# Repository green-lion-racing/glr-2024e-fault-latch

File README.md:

# Fault latch for IMD and BMS/AMS

This board is a fork of [JacobParent7/FSAE_ELECTRONICS](https://github.com/JacobParent7/FSAE_ELECTRONICS/tree/main/Fault%20Latch). Thanks!

### Overview

It is stripped down for our purposes of using it just as a fault latch if either IMD or BMS signal an error. So it can open and close the SDC (Shutdown circuit).

As input it needs +12V and GND. It also takes a high input of both IMD and BMS to register a fault.

It has two outputs for LEDs, these go into the cockpit of the car, to signal issues to the driver.

Lastly there is one connection where the SDC is routed through.

### Used parts

> [!WARNING]  
> Part list is not available currently.

| Article | Description | Link | Quantity |
| ------- | ----------- | ---- | -------- |
|         |             |      |          |
|         |             |      |          |
|         |             |      |          |
|         |             |      |          |
|         |             |      |          |

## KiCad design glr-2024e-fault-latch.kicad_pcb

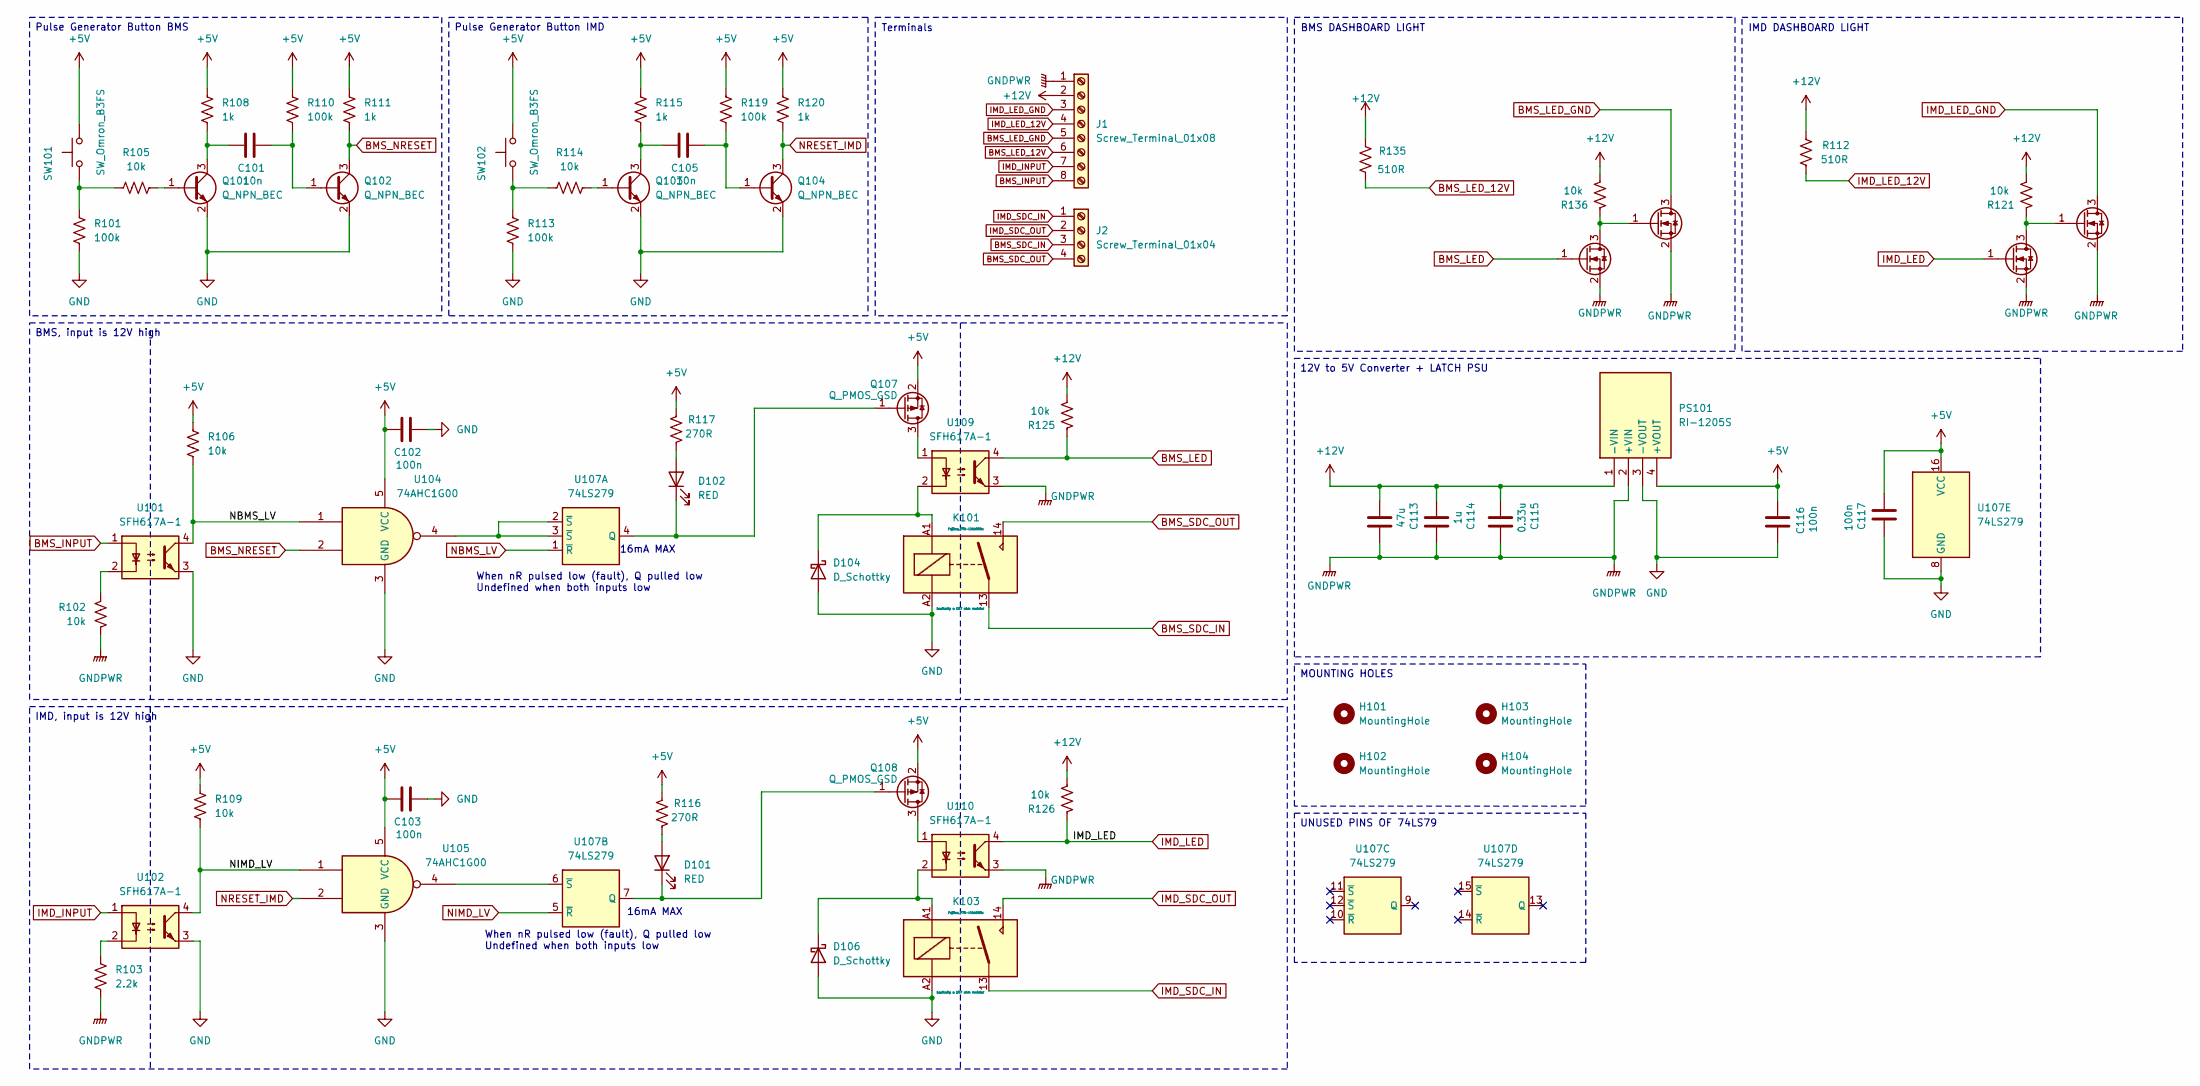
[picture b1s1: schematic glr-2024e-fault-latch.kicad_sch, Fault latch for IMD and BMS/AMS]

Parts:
C101, C105: 10n; C_0603_1608Metric_Pad1.08x0.95mm_HandSolder; JLC# C1589
C102, C103, C116, C117: 100n; C_0603_1608Metric_Pad1.08x0.95mm_HandSolder; JLC# C1591
C113: 47u; CP_Elec_6.3x5.4; JLC# C2836440
C114: 1u; C_0805_2012Metric_Pad1.18x1.45mm_HandSolder; JLC# C91186
C115: 0.33u; C_0603_1608Metric_Pad1.08x0.95mm_HandSolder; JLC# C282682
D101, D102: RED; LED_0805_2012Metric_Pad1.15x1.40mm_HandSolder; JLC# C19171391
D104, D106: D_Schottky; D_SMA; JLC# C8678
H101, H102, H103, H104: MountingHole; MountingHole_3.2mm_M3
J1: Screw_Terminal_01x08; WECO-950-FB-08
J2: Screw_Terminal_01x04; WECO-950-FB-04
K101, K103: Fujitsu_FTR-LYAA005x; Relay_SPST-NO_Fujitsu_FTR-LYAA005x_FormA_Vertical; MOUSER 817-FTR-LYAA005Y
PS101: RI-1205S; RI0505S; Mouser Part Number 919-RI-1205S
Q101, Q102, Q103, Q104: Q_NPN_BEC; SOT-23; JLC# C2146
Q105, Q106, Q114, Q115: Q_NMOS_GSD; SOT-23; JLC# C151421
Q107, Q108: Q_PMOS_GSD; SOT-523; JLC# C96676
R101, R110, R113, R119: 100k; R_0805_2012Metric_Pad1.20x1.40mm_HandSolder; JLC# C149504
R102, R106, R109, R121, R125, R126, R136: 10k; R_0805_2012Metric_Pad1.20x1.40mm_HandSolder; MOUSER ESR10EZPD1002
R103: 2.2k; R_0805_2012Metric_Pad1.20x1.40mm_HandSolder; JLC# C17520
R105, R114: 10k; R_0805_2012Metric_Pad1.20x1.40mm_HandSolder; JLC# C17414
R108, R111, R115, R120: 1k; R_0805_2012Metric_Pad1.20x1.40mm_HandSolder; JLC# C17513
R112, R135: 510R; R_0603_1608Metric; MOUSER KTR03EZPF5100
R116, R117: 270R; R_0805_2012Metric_Pad1.20x1.40mm_HandSolder; JLC# C17590
SW101, SW102: SW_Omron_B3FS; SW_SPST_Omron_B3FS-100xP; JLC# C271750
U101, U102, U109, U110: SFH617A-1; DIP-4_W7.62mm; MOUSER SFH617A-1X007T
U104, U105: 74AHC1G00; SOT-23-5; JLC# C350556
U107: 74LS279; SOIC-16_3.9x9.9mm_P1.27mm; MOUSER 595-SN74LS279ADR

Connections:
+5V: C102.1, C103.1, C116.2, C117.1, PS101.4 (+VOUT), Q107.2 (S), Q108.2 (S), R106.1, R108.1, R109.1, R110.1, R111.1, R115.1, R116.2, R117.2, R119.1, R120.1, SW101.2, SW102.2, U104.5 (VCC), U105.5 (VCC), U107.16 (VCC)
+12V: C113.2, C114.2, C115.2, J1.2, PS101.1 (-VIN), R112.1, R121.1, R125.1, R126.1, R135.1, R136.1
BMS_INPUT: J1.8, U101.1
BMS_LED: Q114.1 (G), R125.2, U109.4
BMS_LED_12V: J1.6, R135.2
BMS_LED_GND: J1.5, Q115.3 (D)
BMS_NRESET: Q102.3 (C), R111.2, U104.2
BMS_SDC_IN: J2.3, K101.13
BMS_SDC_OUT: J2.4, K101.14
GND: C102.2, C103.2, C116.1, C117.2, D104.2 (A), D106.2 (A), K101.A2, K103.A2, PS101.3 (-VOUT), Q101.2 (E), Q102.2 (E), Q103.2 (E), Q104.2 (E), R101.2, R113.2, U101.3, U102.3, U104.3 (GND), U105.3 (GND), U107.8 (GND)
GNDPWR: C113.1, C114.1, C115.1, J1.1, PS101.2 (+VIN), Q105.2 (S), Q106.2 (S), Q114.2 (S), Q115.2 (S), R102.1, R103.2, U109.3, U110.3
IMD_INPUT: J1.7, U102.1
IMD_LED: Q105.1 (G), R126.2, U110.4
IMD_LED_12V: J1.4, R112.2
IMD_LED_GND: J1.3, Q106.3 (D)
IMD_SDC_IN: J2.1, K103.13
IMD_SDC_OUT: J2.2, K103.14
NBMS_LV: R106.2, U101.4, U104.1, U107.1 (~R)
NIMD_LV: R109.2, U102.4, U105.1, U107.5 (~R)
NRESET_IMD: Q104.3 (C), R120.2, U105.2
unnamed: D101.2 (A), R116.1
unnamed: D101.1 (K), Q108.1 (G), U107.7 (Q)
unnamed: D102.2 (A), R117.1
unnamed: D102.1 (K), Q107.1 (G), U107.4 (Q)
unnamed: D104.1 (K), K101.A1, U109.2
unnamed: D106.1 (K), K103.A1, U110.2
unnamed: Q101.1 (B), R105.1
unnamed: C101.1, Q101.3 (C), R108.2
unnamed: C101.2, Q102.1 (B), R110.2
unnamed: Q103.1 (B), R114.1
unnamed: C105.1, Q103.3 (C), R115.2
unnamed: C105.2, Q104.1 (B), R119.2
unnamed: Q105.3 (D), Q106.1 (G), R121.2
unnamed: Q107.3 (D), U109.1
unnamed: Q108.3 (D), U110.1
unnamed: Q114.3 (D), Q115.1 (G), R136.2
unnamed: R101.1, R105.2, SW101.1
unnamed: R102.2, U101.2
unnamed: R103.1, U102.2
unnamed: R113.1, R114.2, SW102.1
unnamed: U104.4, U107.2 (~S), U107.3 (~S)
unnamed: U105.4, U107.6 (~S)

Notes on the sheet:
16mA MAX
When nR pulsed low (fault), Q pulled low Undefined when both inputs low
BMS, input is 12V high
Pulse Generator Button BMS
Terminals
UNUSED PINS OF 74LS79
Pulse Generator Button IMD
12V to 5V Converter + LATCH PSU
MOUNTING HOLES
BMS DASHBOARD LIGHT
IMD, input is 12V high
IMD DASHBOARD LIGHT

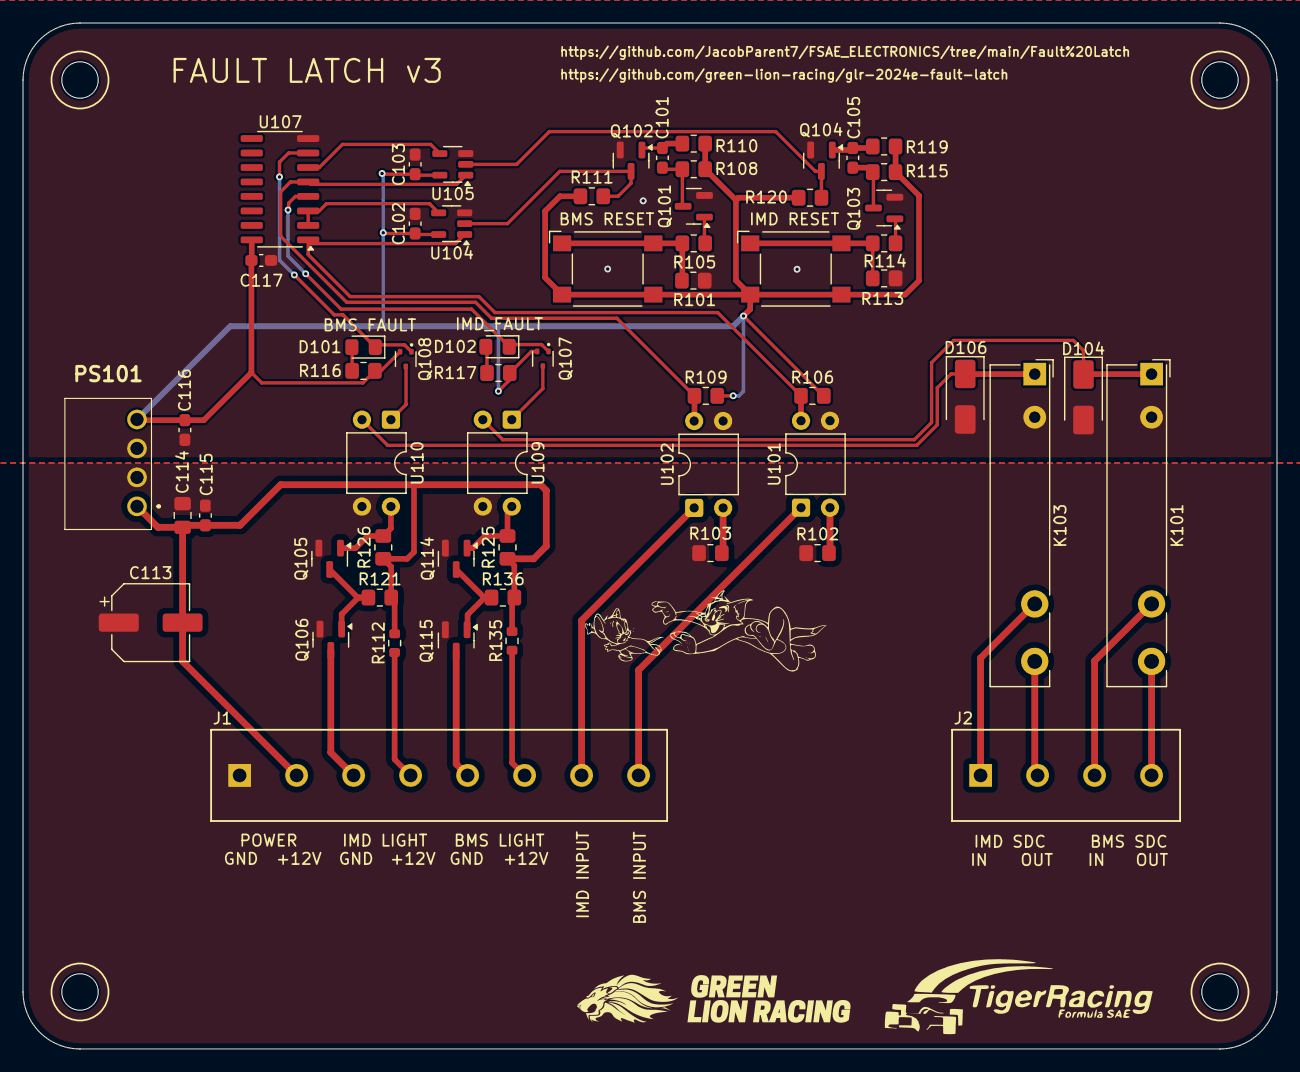
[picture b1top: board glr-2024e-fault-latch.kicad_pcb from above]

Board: 2 copper layers, 110.0 x 90.0 mm, 63 parts (0 on the bottom side), 42 nets.

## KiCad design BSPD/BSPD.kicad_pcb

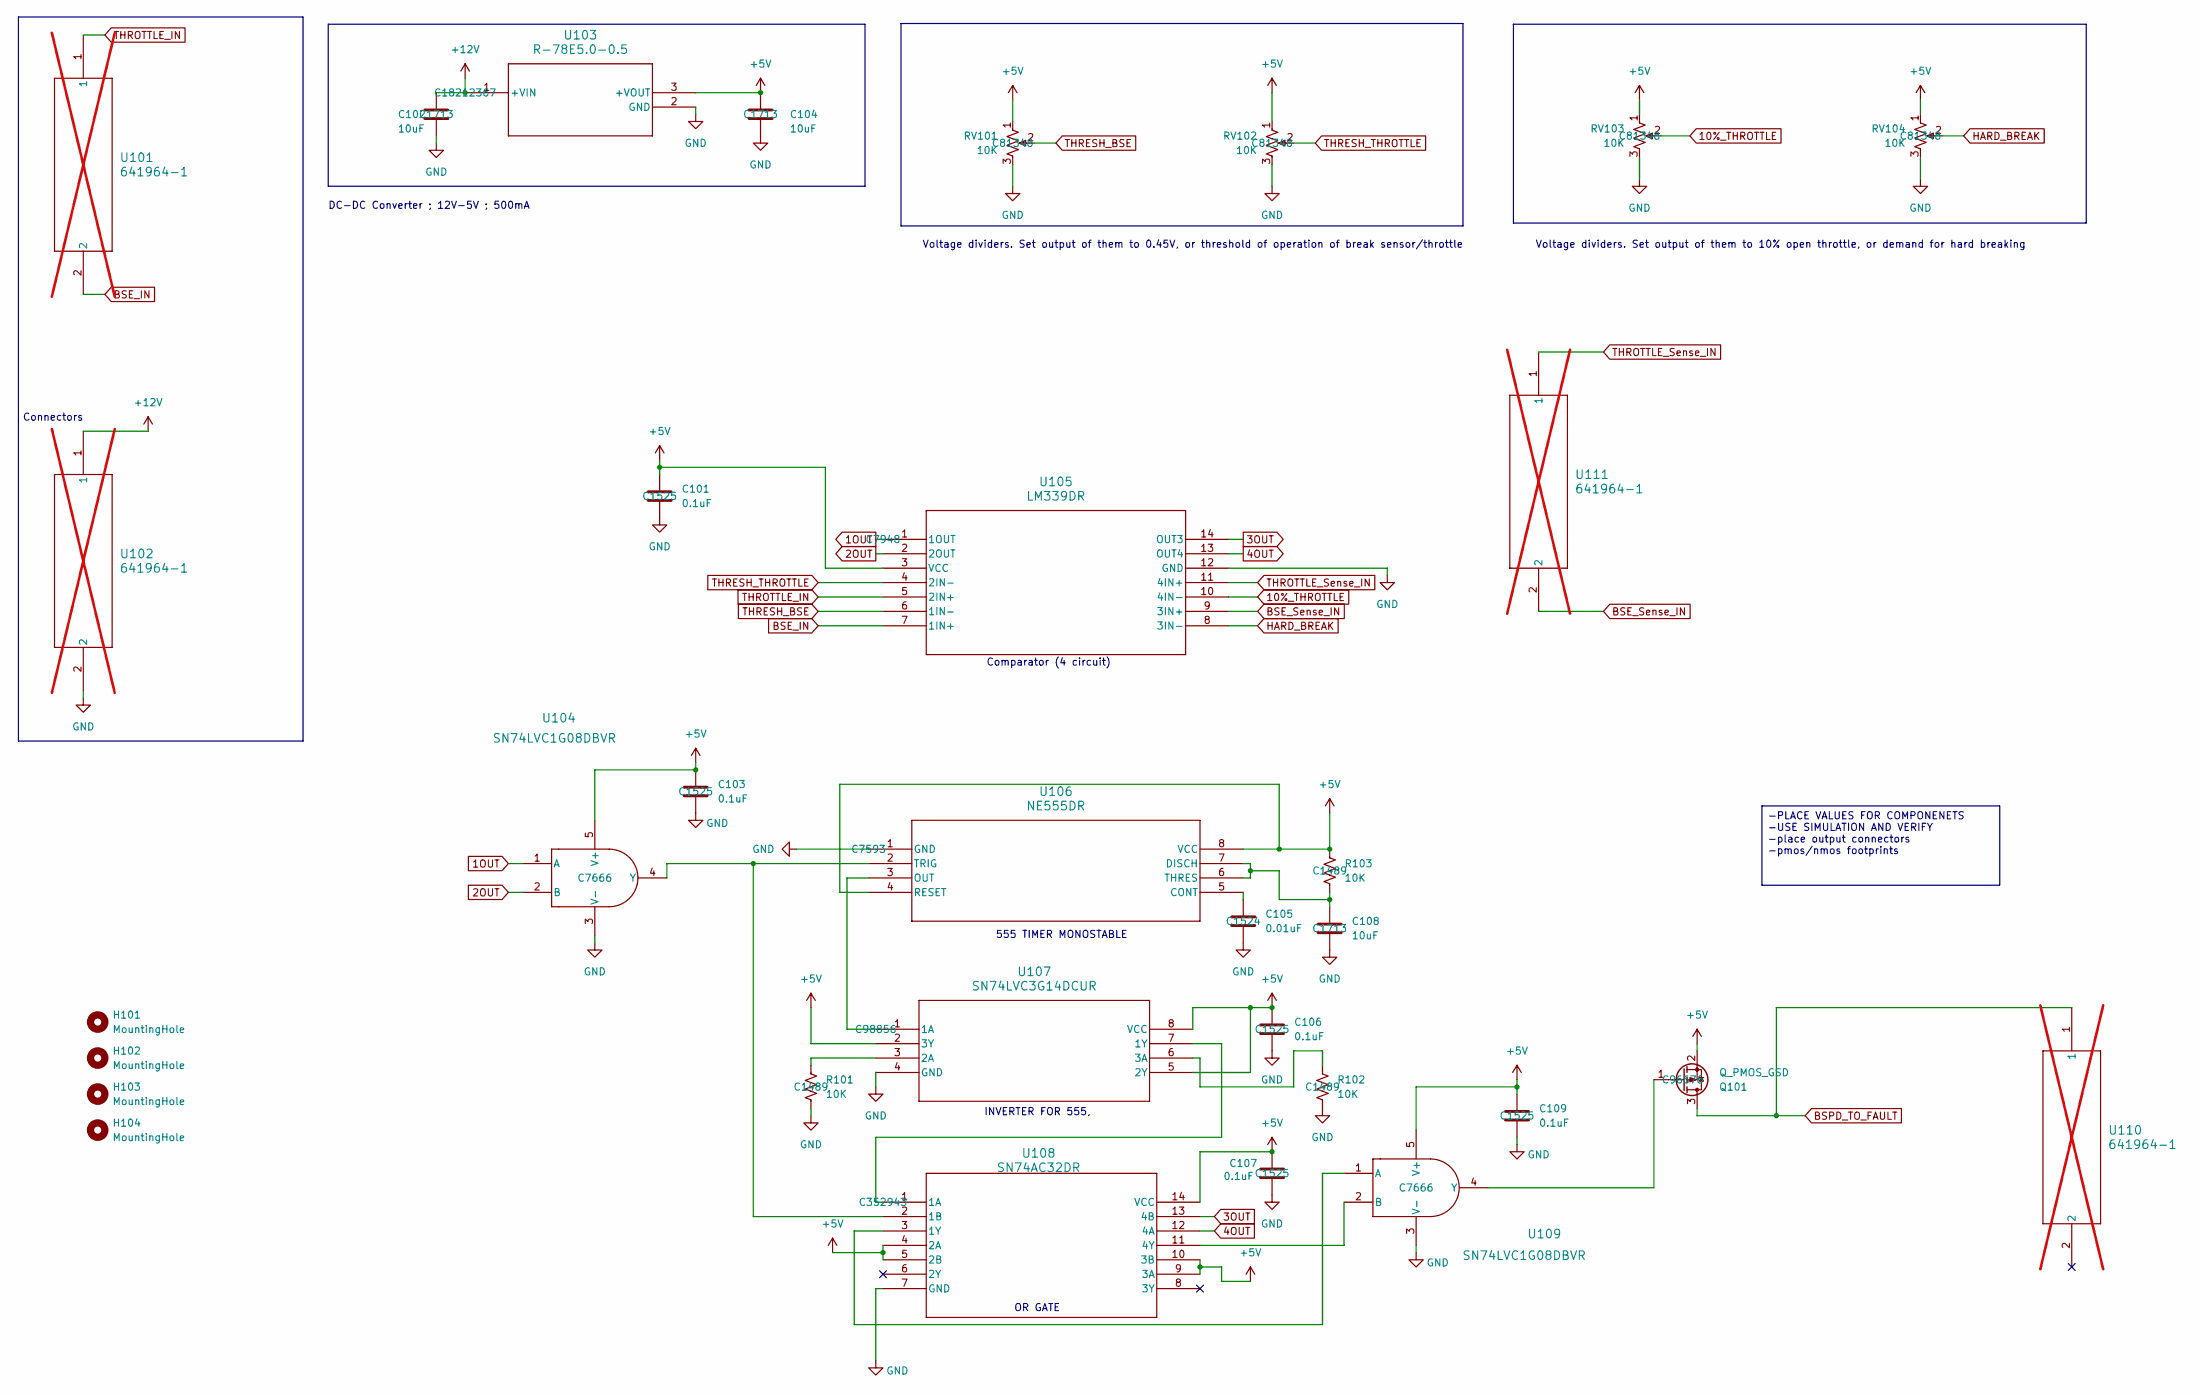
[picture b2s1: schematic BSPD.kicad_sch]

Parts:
C101, C103, C106, C107, C109: 0.1uF; C_0402_1005Metric; JLCPCB Part # C1525
C102, C104, C108: 10uF; C_0805_2012Metric; JLCPCB Part # C1713
C105: 0.01uF; C_0402_1005Metric; JLCPCB Part # C1524
H101, H102, H103, H104: MountingHole; MountingHole_2.2mm_M2
Q101: Q_PMOS_GSD; SOT-523; JLCPCB Part # C96676
R101, R102, R103: 10K; R_1206_3216Metric; JLCPCB Part # C1489
RV101, RV102, RV103, RV104: 10K; POT_3224W; JLCPCB Part # C81348
U101, U102, U110, U111: 641964-1; 641964-1_TYC; not fitted
U103: R-78E5.0-0.5; R-78E-0.5_RCP; JLCPCB Part # C18212367
U104, U109: SN74LVC1G08DBVR; DBV0005A_L; JLCPCB Part # C7666
U105: LM339DR; D14; JLCPCB Part # C7948
U106: NE555DR; D8; JLCPCB Part # C7593
U107: SN74LVC3G14DCUR; DCU8_TEX; JLCPCB Part # C98856
U108: SN74AC32DR; D14; JLCPCB Part # C352943

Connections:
1OUT: U104.1 (A), U105.1 (1OUT)
2OUT: U104.2 (B), U105.2 (2OUT)
3OUT: U105.14 (OUT3), U108.13 (4B)
4OUT: U105.13 (OUT4), U108.12 (4A)
10%_THROTTLE: RV103.2, U105.10 (4IN-)
+5V: C101.1, C103.1, C104.1, C106.1, C107.1, C109.1, Q101.2 (S), R103.1, RV101.1, RV102.1, RV103.1, RV104.1, U103.3 (+VOUT), U104.5 (V+), U105.3 (VCC), U106.4 (RESET), U106.8 (VCC), U107.2 (3Y), U107.5 (2Y), U107.8 (VCC), U108.4 (2A), U108.5 (2B), U108.9 (3A), U108.10 (3B), U108.14 (VCC), U109.5 (V+)
+12V: C102.1, U102.1, U103.1 (+VIN); also elsewhere on the board
BSE_IN: U101.2, U105.7 (1IN+)
BSE_Sense_IN: U105.9 (3IN+), U111.2
BSPD_TO_FAULT: Q101.3 (D), U110.1; also elsewhere on the board
GND: C101.2, C102.2, C103.2, C104.2, C105.2, C106.2, C107.2, C108.2, C109.2, R101.2, R102.2, RV101.3, RV102.3, RV103.3, RV104.3, U102.2, U103.2 (GND), U104.3 (V-), U105.12 (GND), U106.1 (GND), U107.4 (GND), U108.7 (GND), U109.3 (V-); also elsewhere on the board
HARD_BREAK: RV104.2, U105.8 (3IN-)
unnamed 13: Q101.1 (G), U109.4 (Y); also elsewhere on the board
unnamed: U104.4 (Y), U106.2 (TRIG), U108.2 (1B)
unnamed: C105.1, U106.5 (CONT)
unnamed: C108.1, R103.2, U106.6 (THRES), U106.7 (DISCH)
unnamed: U106.3 (OUT), U107.1 (1A)
unnamed: U107.7 (1Y), U108.1 (1A)
unnamed: R101.1, U107.3 (2A)
unnamed: R102.1, U107.6 (3A)
unnamed: U108.3 (1Y), U109.1 (A)
unnamed: U108.11 (4Y), U109.2 (B)
THRESH_BSE: RV101.2, U105.6 (1IN-)
THRESH_THROTTLE: RV102.2, U105.4 (2IN-)
THROTTLE_IN: U101.1, U105.5 (2IN+)
THROTTLE_Sense_IN: U105.11 (4IN+), U111.1

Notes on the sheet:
Comparator (4 circuit)
OR GATE
Voltage dividers. Set output of them to 10% open throttle, or demand for hard breaking
Voltage dividers. Set output of them to 0.45V, or threshold of operation of break sensor/throttle
INVERTER FOR 555,
555 TIMER MONOSTABLE
DC-DC Converter ; 12V-5V ; 500mA
Connectors
-PLACE VALUES FOR COMPONENETS -USE SIMULATION AND VERIFY -place output connectors -pmos/nmos footprints

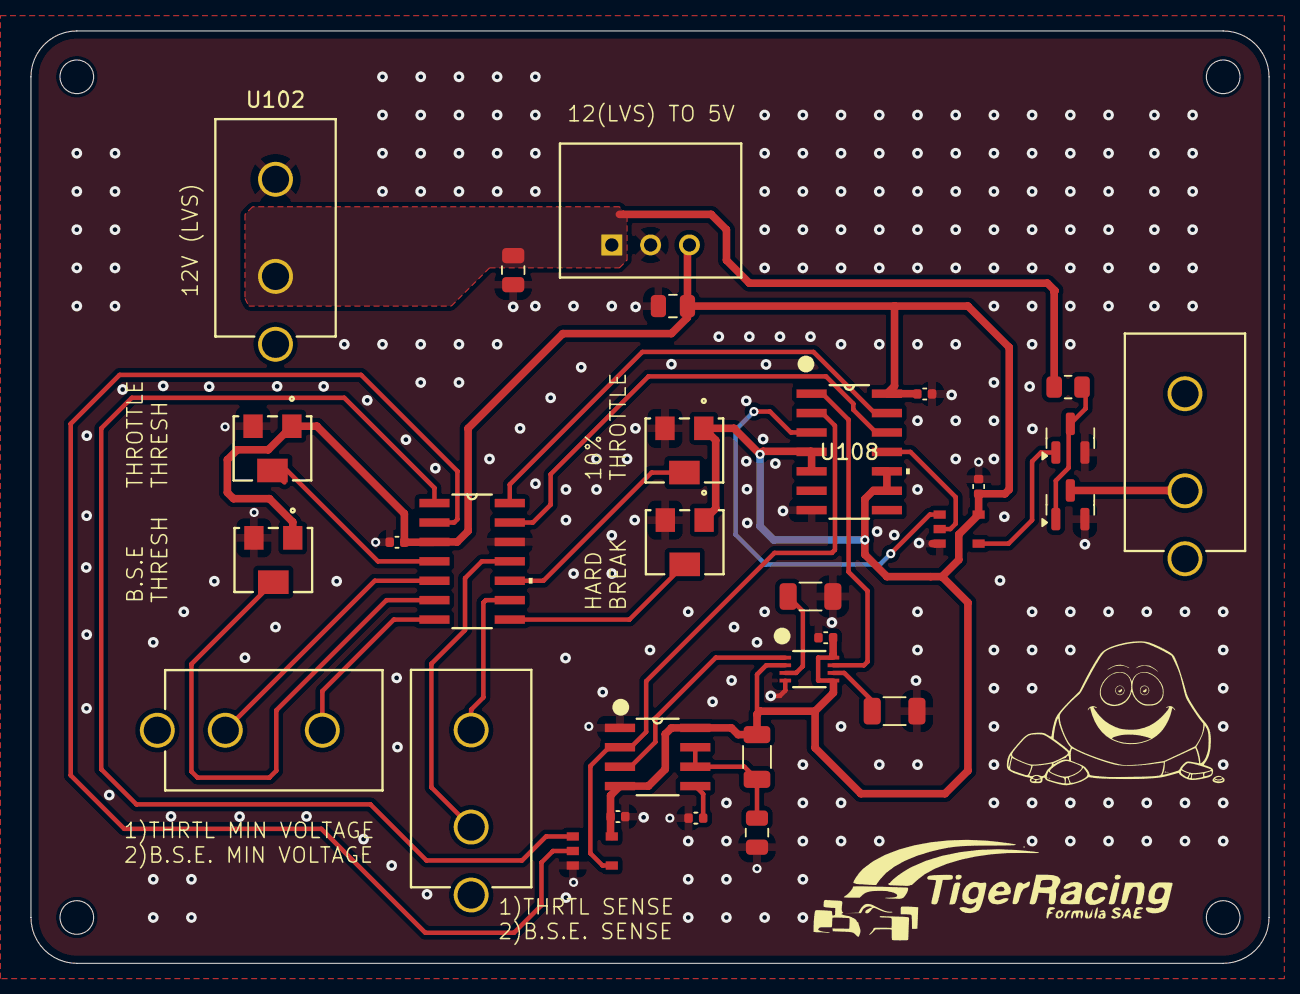
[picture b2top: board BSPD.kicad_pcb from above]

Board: 2 copper layers, 81.0 x 61.0 mm, 34 parts (0 on the bottom side), 27 nets.

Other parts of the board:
Q1, Q2: Q_NMOS_GSD; SOT-23
R1: 10k; R_0805_2012Metric

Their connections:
+12V: R1.1; also elsewhere on the board
BSPD_TO_FAULT: Q2.3 (D); also elsewhere on the board
GND: Q1.2 (S), Q2.2 (S); also elsewhere on the board
unnamed: Q1.3 (D), Q2.1 (G), R1.2
unnamed 13: Q1.1 (G); also elsewhere on the board

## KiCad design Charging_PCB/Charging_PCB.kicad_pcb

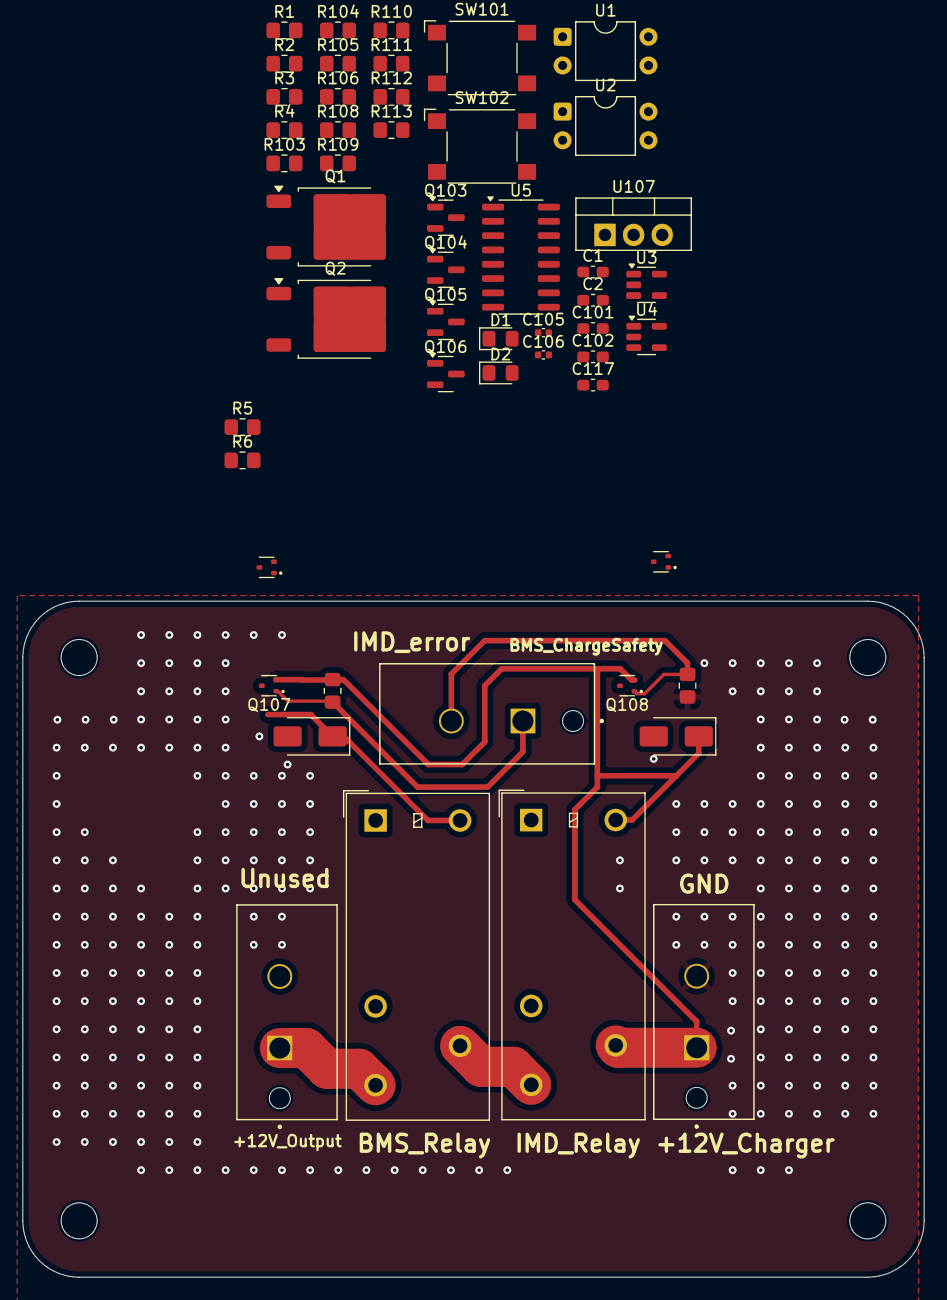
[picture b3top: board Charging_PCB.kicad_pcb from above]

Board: 2 copper layers, 80.0 x 60.0 mm, 56 parts (0 on the bottom side), 31 nets.

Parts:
C1, C2, C117: 100n; C_0603_1608Metric_Pad1.08x0.95mm_HandSolder
C101, C102: 10n; C_0603_1608Metric_Pad1.08x0.95mm_HandSolder
C105: 0.33u; C_0402_1005Metric
C106: 0.01u; C_0402_1005Metric
D1, D2: LED; LED_0805_2012Metric_Pad1.15x1.40mm_HandSolder
D101, D102: D_Schottky; D_SMA
H101, H102, H103, H104: MountingHole; MountingHole_3.2mm_M3
K101, K102: Relay_SPDT_Omron_G2RL-1
Q1, Q2: NMOS; TO-252-2
Q101, Q102, Q107, Q108: Q_PMOS_GSD; SOT-523_Custom(C96676)
Q103, Q104, Q105, Q106: Q_NPN_BEC; SOT-23
R1, R2, R5, R6, R105, R106: 10k; R_0805_2012Metric_Pad1.20x1.40mm_HandSolder
R3, R4: 270; R_0805_2012Metric_Pad1.20x1.40mm_HandSolder
R101: 1K; R_0805_2012Metric_Pad1.20x1.40mm_HandSolder
R102: 2.2K; R_0805_2012Metric_Pad1.20x1.40mm_HandSolder
R103, R104, R110, R112: 100k; R_0805_2012Metric_Pad1.20x1.40mm_HandSolder
R108, R109, R111, R113: 1k; R_0805_2012Metric_Pad1.20x1.40mm_HandSolder
SW101, SW102: SW_Omron_B3FS; SW_SPST_Omron_B3FS-100xP
U1, U2: SFH617A-1; DIP-4_W7.62mm
U3, U4: 74AHC1G00; SOT-23-5
U5: 74LS279; SOIC-16_3.9x9.9mm_P1.27mm
U101, U102, U103: 641964-1; TE_641964-1
U107: LM7805_TO220; TO-220-3_Vertical

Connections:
+5V: C1.1, C2.1, C106.1, C117.1, R1.1, R2.1, R3.1, R4.1, R108.1, R109.1, R110.1, R111.1, R112.1, R113.1, SW101.2, SW102.2, U3.3 (GND), U4.3 (GND), U5.16 (VCC), U107.3 (VO)
+12V: C105.1, D101.1 (K), D102.1 (K), K101.A2, K102.11, K102.A2, Q101.2 (S), Q102.2 (S), Q107.2 (S), Q108.2 (S), R101.1, U102.1, U107.1 (VI)
/+12_Relay: K101.14, U103.1
/BMS_CSO: Q107.1 (G), R101.2, U101.1
/BMS_RESET: Q104.3 (C), R111.2, U4.1, U5.1 (~R)
/IMD_Error: Q108.1 (G), R102.1, U101.2
/IMD_RESET: Q106.3 (C), R113.2, U3.1, U5.10 (~R)
GND: C1.2, C2.2, C105.2, C106.2, C117.2, Q1.3 (S), Q2.3 (S), Q103.2 (E), Q104.2 (E), Q105.2 (E), Q106.2 (E), R5.2, R6.2, R102.2, R103.2, R104.2, U1.2, U1.3, U2.2, U2.3, U3.5 (VCC), U4.5 (VCC), U5.8 (GND), U102.2, U107.2 (GND)
unnamed: D1.2 (A), R3.2
unnamed: D1.1 (K), Q1.2 (G), U5.4 (Q)
unnamed: D2.2 (A), R4.2
unnamed: D2.1 (K), Q2.2 (G), U5.9 (Q)
unnamed: D101.2 (A), K101.A1, Q1.1 (D)
unnamed: D102.2 (A), K102.A1, Q2.1 (D)
unnamed: K101.11, K102.14
unnamed: Q101.3 (D), U1.1
unnamed: Q101.1 (G), Q107.3 (D), R5.1
unnamed: Q102.3 (D), U2.1
unnamed: Q102.1 (G), Q108.3 (D), R6.1
unnamed: Q103.1 (B), R105.1
unnamed: C101.1, Q103.3 (C), R108.2
unnamed: C101.2, Q104.1 (B), R110.2
unnamed: Q105.1 (B), R106.1
unnamed: C102.1, Q105.3 (C), R109.2
unnamed: C102.2, Q106.1 (B), R112.2
unnamed: R1.2, U1.4, U4.2
unnamed: R2.2, U2.4, U3.2
unnamed: R103.1, R105.2, SW101.1
unnamed: R104.1, R106.2, SW102.1
unnamed: U3.4, U5.11 (~S), U5.12 (~S)
unnamed: U4.4, U5.2 (~S), U5.3 (~S)

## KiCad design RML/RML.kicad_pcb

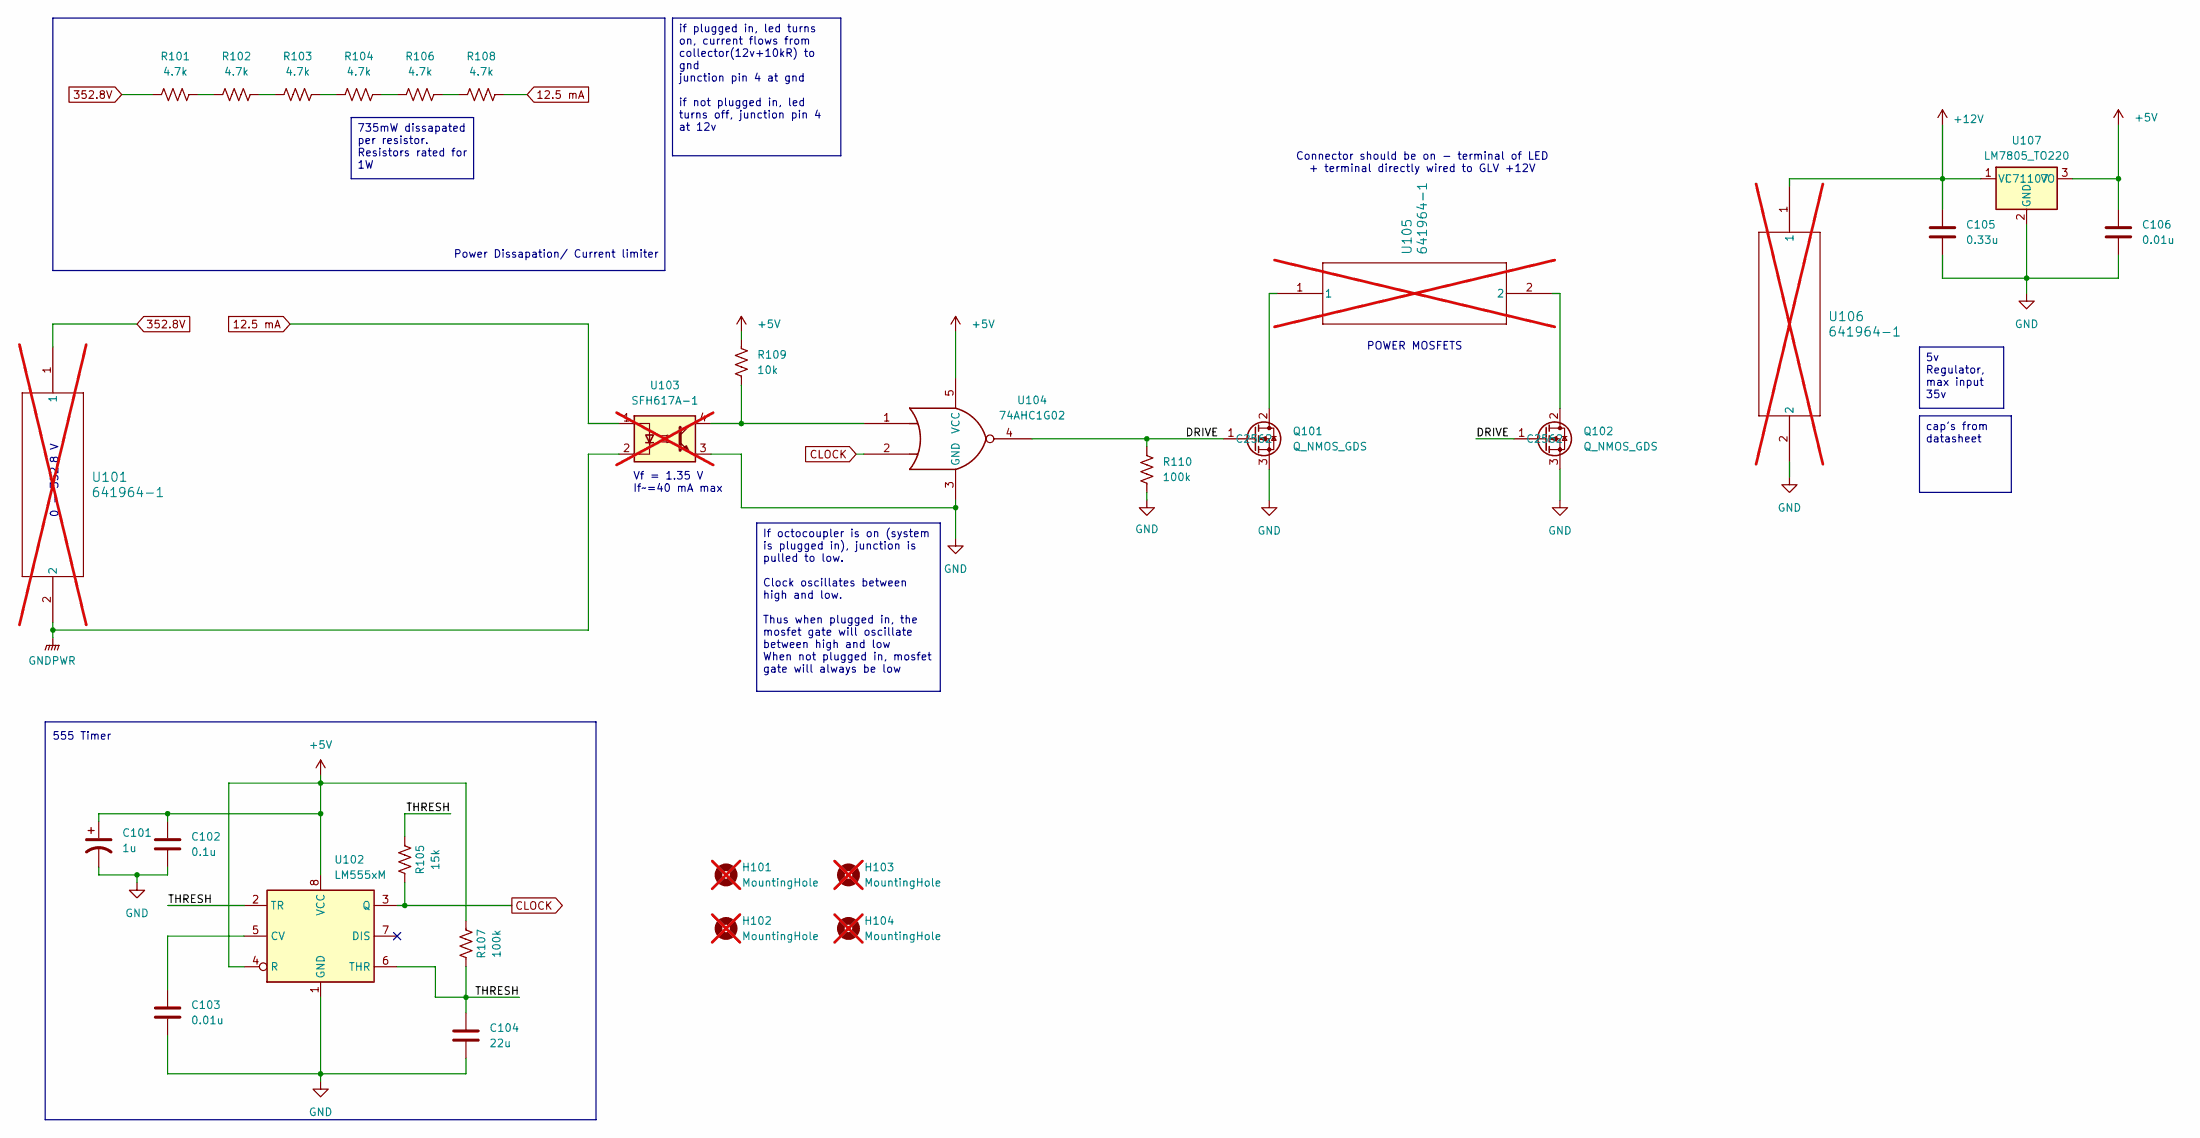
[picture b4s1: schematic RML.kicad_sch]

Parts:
C101: 1u; C_0603_1608Metric; JLC# C59782
C102: 0.1u; C_0402_1005Metric; JLC# C133086
C103, C106: 0.01u; C_0402_1005Metric; JLC# C15195
C104: 22u; C_0402_1005Metric; JLC# C105226
C105: 0.33u; C_0402_1005Metric; JLC# C107013
H101, H102, H103, H104: MountingHole; MountingHole_3.2mm_M3; not fitted
Q101, Q102: Q_NMOS_GDS; TO-220-3_Vertical; JLC# C2562
R101, R102, R103, R104, R106, R108: 4.7k; R_2512_6332Metric_Pad1.40x3.35mm_HandSolder; JLC# C163339
R105: 15k; C_0402_1005Metric; JLC# C25756
R107, R110: 100k; C_0402_1005Metric; JLC# C102750
R109: 10k; C_0402_1005Metric; JLC# C102759
U101, U105, U106: 641964-1; 641964-1_TYC; not fitted
U102: LM555xM; SOIC-8_3.9x4.9mm_P1.27mm; JLC# C90760
U103: SFH617A-1; DIP-4_W7.62mm; not fitted
U104: 74AHC1G02; SOT-23-5; JLC# C7463
U107: LM7805_TO220; TO-220-3_Vertical; JLC# C71107

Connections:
12.5 mA: R108.1, U103.1
352.8V: R101.2, U101.1
+5V: C101.1, C102.1, C106.1, R107.2, R109.1, U102.4 (R), U102.8 (VCC), U104.5 (VCC), U107.3 (VO)
+12V: C105.1, U106.1, U107.1 (VI)
/DRIVE: Q101.1 (G), Q102.1 (G), R110.2, U104.4
/THRESH: C104.2, R105.2, R107.1, U102.2 (TR), U102.6 (THR)
CLOCK: R105.1, U102.3 (Q), U104.2
GND: C101.2, C102.2, C103.2, C104.1, C105.2, C106.2, Q101.3 (S), Q102.3 (S), R110.1, U102.1 (GND), U103.3, U104.3 (GND), U106.2, U107.2 (GND)
GNDPWR: U101.2, U103.2
unnamed: Q101.2 (D), U105.1
unnamed: Q102.2 (D), U105.2
unnamed: R101.1, R102.2
unnamed: R102.1, R103.2
unnamed: R103.1, R104.2
unnamed: R104.1, R106.2
unnamed: R106.1, R108.2
unnamed: R109.2, U103.4, U104.1
unnamed: C103.1, U102.5 (CV)

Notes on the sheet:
555 Timer
POWER MOSFETS
Connector should be on - terminal of LED + terminal directly wired to GLV +12V
0 - 352.8 V
Vf = 1.35 V If~=40 mA max
Power Dissapation/ Current limiter
if plugged in, led turns on, current flows from collector(12v+10kR) to gnd junction pin 4 at gnd if not plugged in, led turns off, junction pin 4 at 12v
cap's from datasheet
5v Regulator, max input 35v
735mW dissapated per resistor. Resistors rated for 1W
If octocoupler is on (system is plugged in), junction is pulled to low. Clock oscillates between high and low. Thus when plugged in, the mosfet gate will oscillate between high and low When not plugged in, mosfet gate will always be low

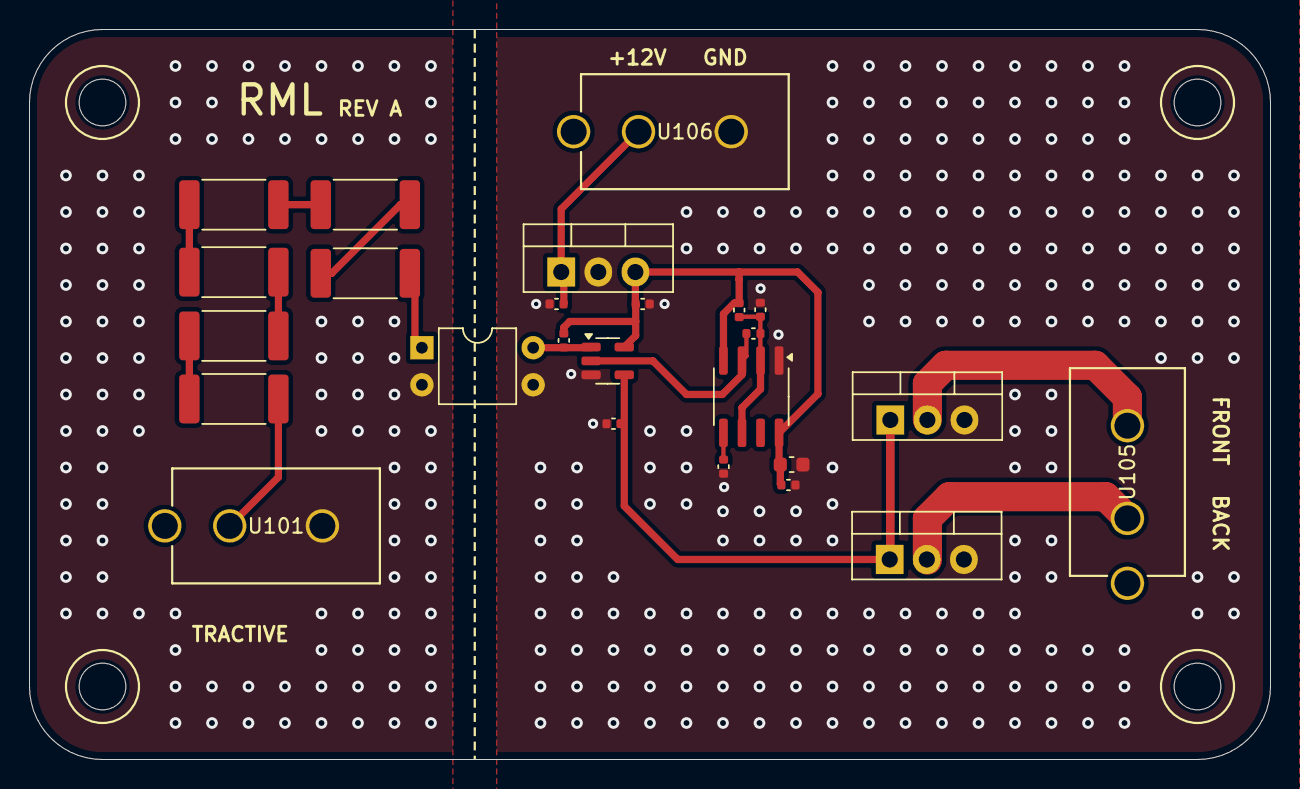
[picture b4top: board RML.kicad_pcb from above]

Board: 4 copper layers, 85.0 x 50.0 mm, 29 parts (0 on the bottom side), 18 nets.

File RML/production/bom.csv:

Designator,Footprint,Quantity,Value,LCSC Part #
C101,0603,1,1u,
C102,0402,1,0.1u,
"C103, C106",0402,2,0.01u,
C104,0402,1,22u,
C105,0402,1,0.33u,
"H101, H102, H103, H104",MountingHole_3.2mm_M3,4,MountingHole,
"Q101, Q102",TO-220-3_Vertical,2,Q_NMOS_GDS,
"R101, R102, R103, R104, R106, R108",2512,6,4.7k,
R105,0402,1,15k,
"R107, R110",0402,2,100k,
R109,0402,1,10k,
"U101, U105, U106",641964-1_TYC,3,641964-1,
U102,SOIC-8_3.9x4.9mm_P1.27mm,1,LM555xM,
U103,DIP-4_W7.62mm,1,SFH617A-1,
U104,SOT-23-5,1,74AHC1G02,
U107,TO-220-3_Vertical,1,LM7805_TO220,
